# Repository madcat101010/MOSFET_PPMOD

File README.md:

# SPECIFICATIONS
PROJECT: MOSFET_PPMod

REV: 1.0

AUTHOR: ROBIN Y

DATE: XX XXX 20XX

PCB SOFTWARE: KiCAD X.X.X

DIMENSIONS: 1,920 mil x 2,500 mil

LAYERS: 2

# NOTES:
Basic MOSFET based pulsed power module. Old design. Just putting it on Github for personal archiving.

Specs are probably off and I need to add the tuned values that filters out switching ringing.

Custom foorprints in .pretty included.

This is an open source hardware project. No warranties or guarantees. Use this design at your own risk!

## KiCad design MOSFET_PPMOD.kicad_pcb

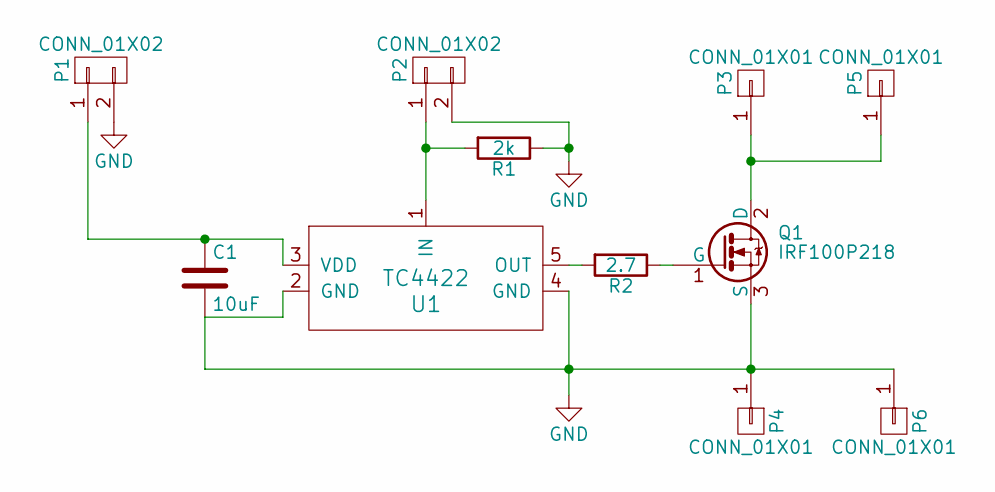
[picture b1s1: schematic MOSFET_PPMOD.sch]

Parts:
C1: 10uF; C_0805_HandSoldering
P1, P2: CONN_01X02; JST_XH_B02B-XH-A_02x2.50mm_Straight
P3, P4, P5, P6: CONN_01X01; M5_STUD
Q1: IRF100P218; TO-247-3_Specced
R1: 2k; C_0805_HandSoldering
R2: 2.7; C_0805_HandSoldering
U1: TC4422; TO-220-5_Specced

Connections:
GND: C1.2, P1.2, P2.2, P4.1, P6.1, Q1.3 (S), R1.1, U1.2 (GND), U1.4 (GND)
unnamed: C1.1, P1.1, U1.3 (VDD)
unnamed: P2.1, R1.2, U1.1 (IN)
unnamed: P3.1, P5.1, Q1.2 (D)
unnamed: Q1.1 (G), R2.1
unnamed: R2.2, U1.5 (OUT)

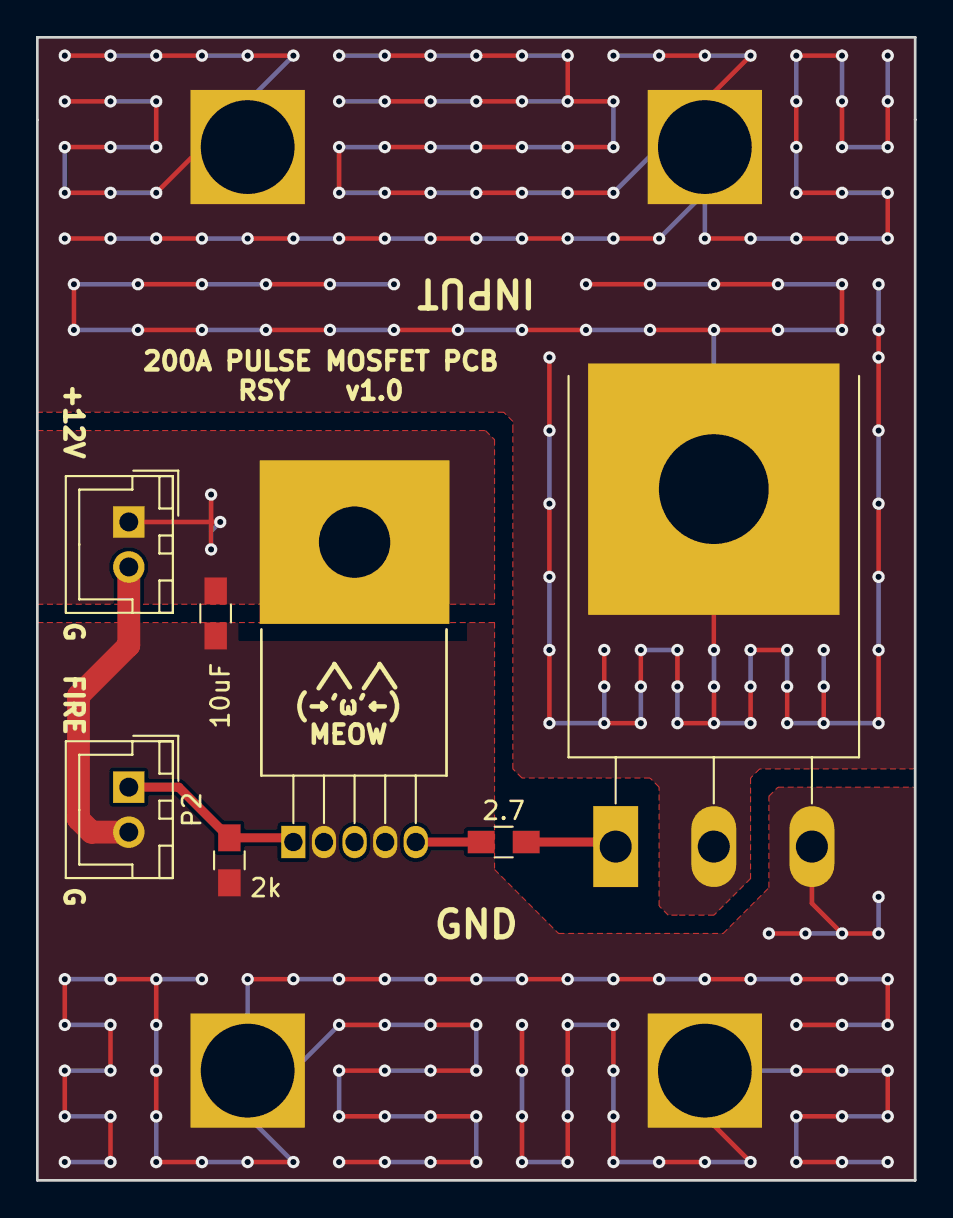
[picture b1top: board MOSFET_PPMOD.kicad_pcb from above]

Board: 2 copper layers, 48.8 x 63.5 mm, 11 parts (0 on the bottom side), 6 nets.

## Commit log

2021-04-06 initting repo
